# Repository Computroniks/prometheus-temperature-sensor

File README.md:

<!-- 
SPDX-FileCopyrightText: 2023-2024 Sidings Media <contact@sidingsmedia.com>
SPDX-License-Identifier: MIT
-->

# Prometheus Temperature Sensor

A WiFi enabled temperature and humidity sensor built around an ESP8266
module with a Prometheus metrics endpoint.

## Hardware

The PCB is designed to be made with entirely through hole components to
make DIY assembly easy without having to mess around with fiddly SMD
components.

### Design

#### MCU

The ESP-01 module has been used to control the sensor. This is a small
module based upon the ESP8266. 

#### Temperature / Humidity Sensor

The temperature / humidity sensor that we have used for this design is
the AHT10 although any sensor that works with 3.3V and uses I2C could
probably be made to work.

#### Power

You can power the board in 3 different ways. There is a DC jack, a USB
connector (this also doubles as a serial interface for configuration)
and finally a JST battery connector to allow make the sensor portable.
All power inputs support from 4-12V DC. Power is regulated using a
MCP1702 low dropout regulator to minimize the voltage drop from power
input to the board power supply. Each input has a 1n5817 diode on the
positive input to prevent reverse powering of devices. This does also
induce a slight voltage drop so you may require a power supply slightly
above 4V, perhaps 4.5V.

### Design Software

The schematic and board design were both drawn using
[KiCad](https://www.kicad.org/), an open source electronic design
automation suite.

## Firmware

### Build Environment

#### Toolchain and SDK

You will need to setup both the toolchain for the ESP8266 as well as the
[ESP8266 RTOS SDK](https://github.com/espressif/ESP8266_RTOS_SDK).
Espressif provide documentation for the setup of both components.

* [Toolchain Setup](https://docs.espressif.com/projects/esp8266-rtos-sdk/en/latest/get-started/index.html#setup-toolchain)
* [SDK Setup](https://docs.espressif.com/projects/esp8266-rtos-sdk/en/latest/get-started/index.html#get-esp8266-rtos-sdk)

#### Environment Variables

Two environment variables are used to tell `esptool.py` (the tool used
by the SDK to flash your firmware to the ESP8266) where to flash to and
at what speed.

* `ESPPORT` - This is the path to the device to program, e.g.
  `/dev/ttyUSB0`.
* `ESPBAUD` - Baud rate to communicate at. Should normally be set to
  `115200` for flashing.

If you encounter an error such as below when running `make flash` you
probably need to set the `ESPPORT` environment variable.

```
A fatal error occurred: Cannot find target port named 'None'.
CMake Error at run_esptool.cmake:45 (message):
  esptool.py failed
```
#### Other requirements

You will also need CMake and Make installed to compile and flash the
firmware.

### Build and flash

#### Initialize build system

First create a build directory in src and cd into it.

```
mkdir build
cd build
```

Then you can run CMake to generate the build system.

```
cmake ../src
```

#### Compile and upload

To compile the firmware run:

```
make
```

And to upload to the board run:

```
make flash
```

`make flash` will also compile the firmware before it uploads it to the
board, so you can omit running `make` separately if you like.

## Licence
This repo uses the [REUSE](https://reuse.software) standard in order to
communicate the correct licence for the file. For those unfamiliar with
the standard the licence for each file can be found in one of three
places. The licence will either be in a comment block at the top of the
file, in a `.license` file with the same name as the file, or in the
dep5 file located in the `.reuse` directory. If you are unsure of the
licencing terms please contact
[mnickson@sidingsmedia.com](mailto:mnickson@sidingsmedia.com).
All files committed to this repo must contain valid licencing
information or the pull request can not be accepted.

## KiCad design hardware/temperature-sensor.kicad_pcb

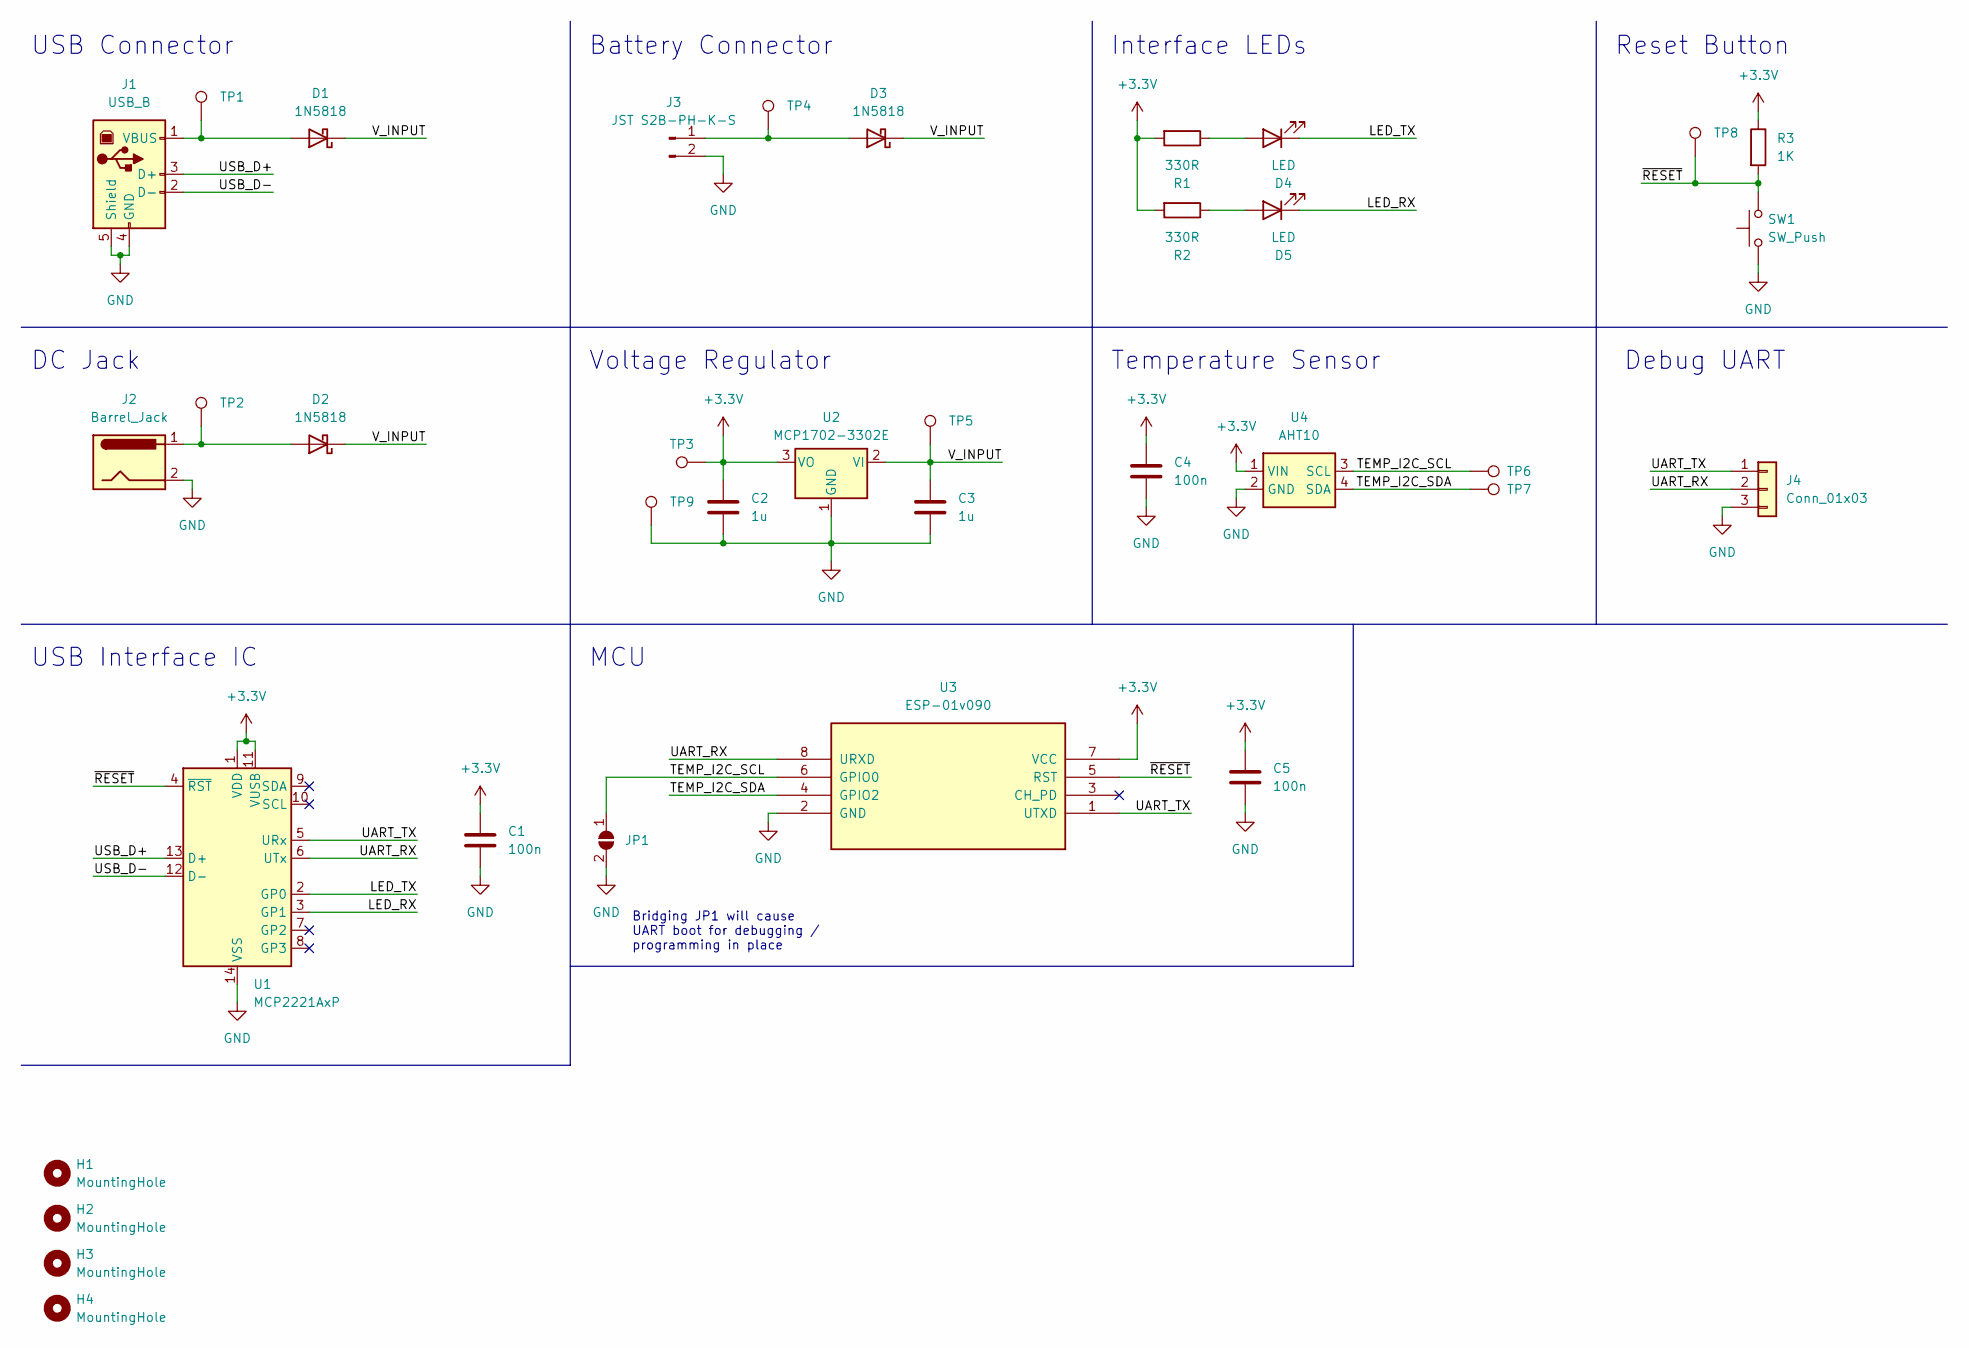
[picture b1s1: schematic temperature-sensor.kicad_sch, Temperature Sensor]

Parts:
C1, C4, C5: 100n; C_Disc_D5.1mm_W3.2mm_P5.00mm
C2, C3: 1u; C_Disc_D5.1mm_W3.2mm_P5.00mm
D1, D2, D3: 1N5818; D_DO-41_SOD81_P10.16mm_Horizontal
D4, D5: LED; LED_D3.0mm
H1, H2, H3, H4: MountingHole; MountingHole_3.2mm_M3
J1: USB_B; USB_B_Lumberg_2411_02_Horizontal
J2: Barrel_Jack; BarrelJack_Horizontal
J3: JST S2B-PH-K-S; JST_PH_S2B-PH-K_1x02_P2.00mm_Horizontal
J4: Conn_01x03; PinHeader_1x03_P2.54mm_Vertical
JP1: SolderJumper_2_Open; SolderJumper-2_P1.3mm_Open_Pad1.0x1.5mm
R1, R2: 330R; R_Axial_DIN0207_L6.3mm_D2.5mm_P7.62mm_Horizontal
R3: 1K; R_Axial_DIN0207_L6.3mm_D2.5mm_P7.62mm_Horizontal
SW1: SW_Push; SW_PUSH_6mm
TP1, TP2, TP3, TP4, TP5, TP6, TP7, TP8, TP9: TestPoint; TestPoint_Pad_D2.0mm
U1: MCP2221AxP; DIP-14_W7.62mm
U2: MCP1702-3302E; TO-92_Inline
U3: ESP-01v090; ESP-01
U4: AHT10

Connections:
+3.3V: C1.1, C2.1, C4.1, C5.1, R1.2, R2.2, R3.1, TP3.1, U1.1 (VDD), U1.11 (VUSB), U2.3 (VO), U3.7 (VCC), U4.1 (VIN)
/LED_RX: D5.1 (K), U1.3 (GP1)
/LED_TX: D4.1 (K), U1.2 (GP0)
/TEMP_I2C_SCL: JP1.1 (A), TP6.1, U3.6 (GPIO0), U4.3 (SCL)
/TEMP_I2C_SDA: TP7.1, U3.4 (GPIO2), U4.4 (SDA)
/UART_RX: J4.2, U1.6 (UTx), U3.8 (URXD)
/UART_TX: J4.1, U1.5 (URx), U3.1 (UTXD)
/USB_D+: J1.3 (D+), U1.13 (D+)
/USB_D-: J1.2 (D-), U1.12 (D-)
/V_INPUT: C3.1, D1.1 (K), D2.1 (K), D3.1 (K), TP5.1, U2.2 (VI)
/~RESET: R3.2, SW1.2, TP8.1, U1.4 (~RST), U3.5 (RST)
GND: C1.2, C2.2, C3.2, C4.2, C5.2, J1.4 (GND), J1.5 (Shield), J2.2, J3.2, J4.3, JP1.2 (B), SW1.1, TP9.1, U1.14 (VSS), U2.1 (GND), U3.2 (GND), U4.2 (GND)
unnamed: D1.2 (A), J1.1 (VBUS), TP1.1
unnamed: D2.2 (A), J2.1, TP2.1
unnamed: D3.2 (A), J3.1, TP4.1
unnamed: D4.2 (A), R1.1
unnamed: D5.2 (A), R2.1

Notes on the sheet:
Bridging JP1 will cause UART boot for debugging / programming in place
Debug UART
Battery Connector
USB Connector
Voltage Regulator
Reset Button
DC Jack
USB Interface IC
MCU
Interface LEDs
Temperature Sensor

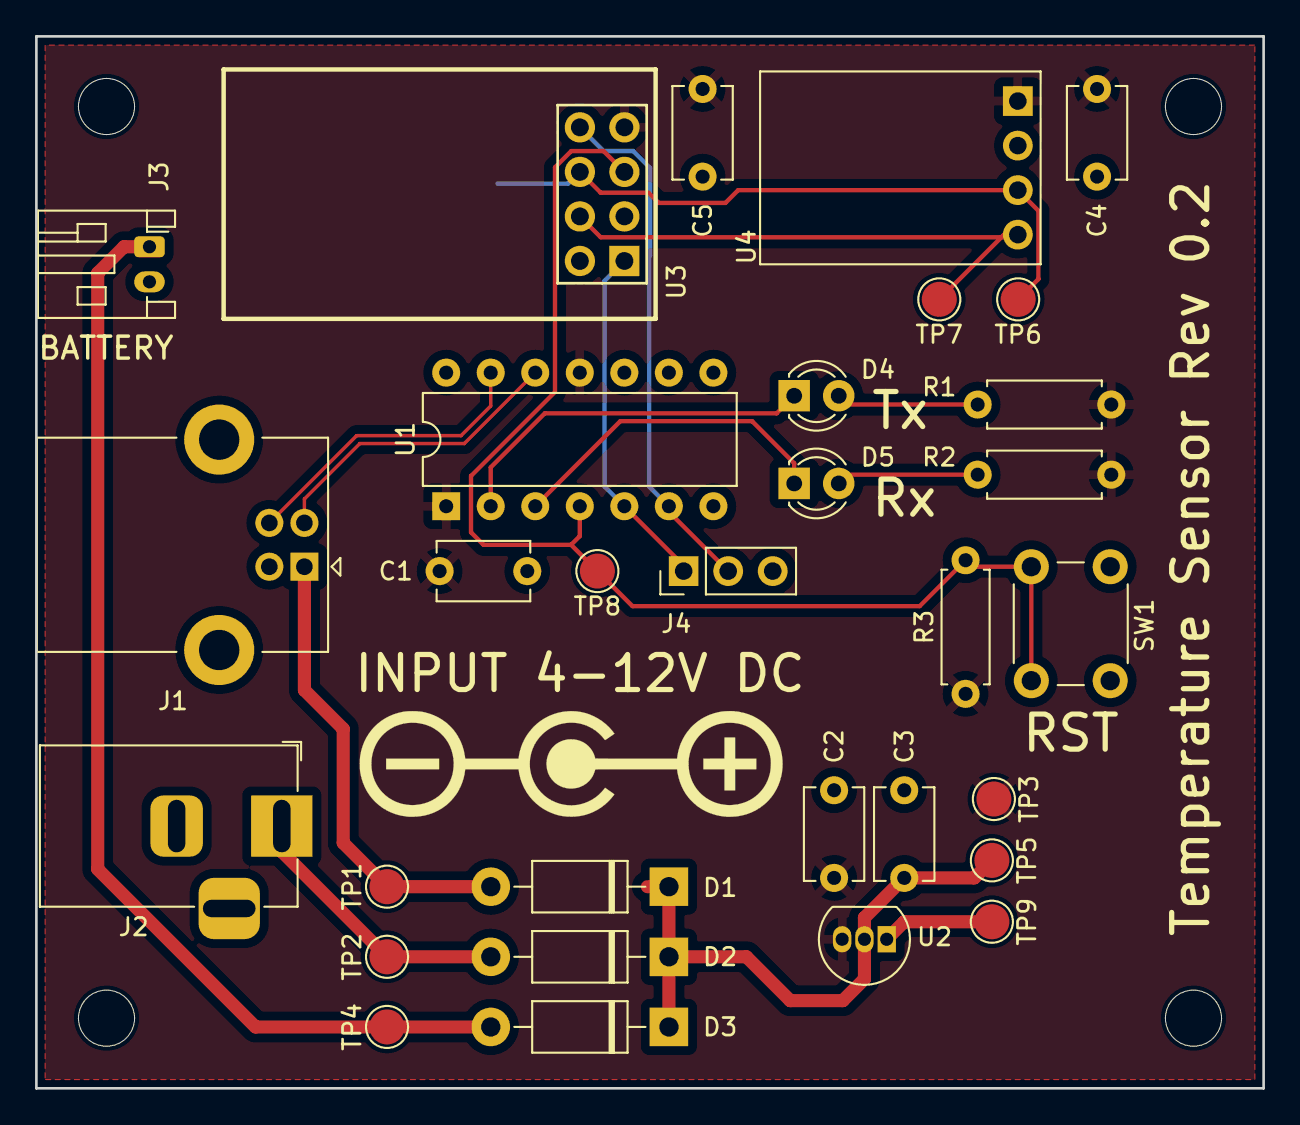
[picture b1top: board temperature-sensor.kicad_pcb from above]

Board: 2 copper layers, 70.0 x 60.0 mm, 36 parts (1 on the bottom side), 17 nets.

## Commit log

2024-01-08 Initial repo setup
2024-01-08 Initial hardware design
2024-01-11 Added readme images
2024-01-12 Added correct 3D models
2024-01-13 Rev 0.2 - Added jumper to support UART boot
2024-01-13 Fixed fab references
2024-01-13 Seperated out .gitignore
2024-01-13 Changed location for build system
2024-01-13 Added build system
2024-01-13 Separated I2C tracks
2024-01-13 Added AHT10 control
2024-01-13 Lookup error codes
2024-01-13 Enabled SPIFFS filesystem
2024-01-13 Created required files
2024-01-16 Added initial config setting via UART
    Not quite complete yet though as still some issues with setting wifi
2024-01-18 Fixed UART update wifi settings
2024-01-18 Fixed reuse compliance
2024-01-20 Added initial WLAN config
2024-01-20 Fixed partition size
2024-01-20 Added editorconfig + formatted
2024-01-20 Added SDK defaults
2024-01-20 Slight changes to logging
2024-01-20 Added UART commands for new provisioning
2024-01-20 Added provision for multiple access to sensor
2024-01-20 Fixed sensor not being released after measure
2024-01-20 Enabled sensor access through UART
2024-01-20 Enabled get uptime from UART
2024-01-20 Initial web sever config
2024-01-20 Added memory usage to metrics
2024-01-21 Slight improvements to error handling

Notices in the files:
hardware/temperature-sensor.kicad_pcb:
Licence: CERN-OHL-P-2.0 or any later version
Licenced under CERN-OHL-P-2.0
